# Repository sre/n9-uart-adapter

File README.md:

# N9 UART/Debug Adapter

Kernel developers like to have UART access to their embedded boards for
debugging purposes. While the Nokia N900 and N950 had the pads available
under their battery, Nokia N9 has them inside its SIM-card slot. This
project contains PCB design for KiCAD, which can be used to access the
UART pads.

To get the PCB into a functional state so called "spring fingers" must
be soldered to the rectangular pads.

# License

ISC License

Copyright (c) 2017 Sebastian Reichel <sre@kernel.org>

Permission to use, copy, modify, and/or distribute this software for any
purpose with or without fee is hereby granted, provided that the above
copyright notice and this permission notice appear in all copies.

THE SOFTWARE IS PROVIDED "AS IS" AND THE AUTHOR DISCLAIMS ALL WARRANTIES WITH
REGARD TO THIS SOFTWARE INCLUDING ALL IMPLIED WARRANTIES OF MERCHANTABILITY
AND FITNESS. IN NO EVENT SHALL THE AUTHOR BE LIABLE FOR ANY SPECIAL, DIRECT,
INDIRECT, OR CONSEQUENTIAL DAMAGES OR ANY DAMAGES WHATSOEVER RESULTING FROM
LOSS OF USE, DATA OR PROFITS, WHETHER IN AN ACTION OF CONTRACT, NEGLIGENCE
OR OTHER TORTIOUS ACTION, ARISING OUT OF OR IN CONNECTION WITH THE USE OR
PERFORMANCE OF THIS SOFTWARE.

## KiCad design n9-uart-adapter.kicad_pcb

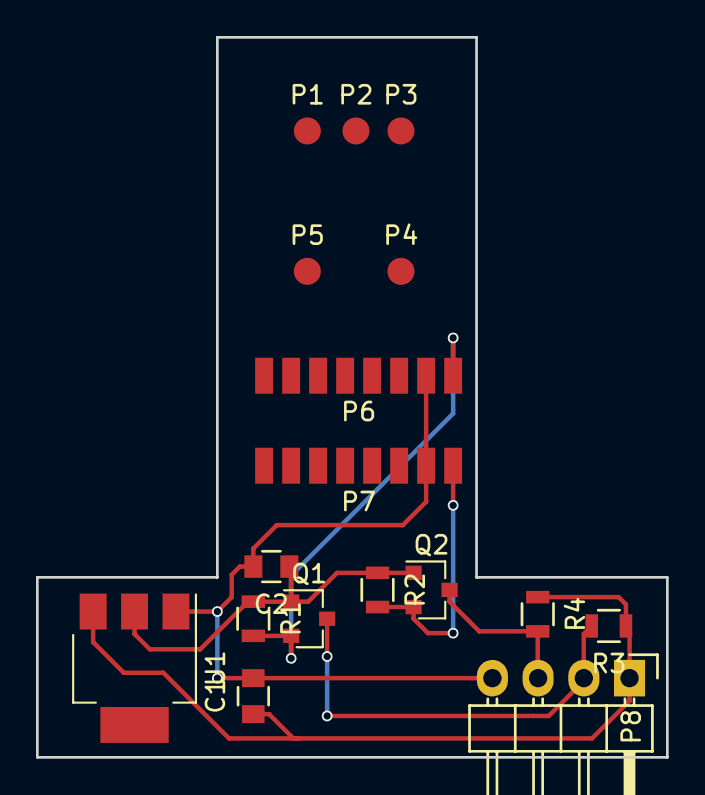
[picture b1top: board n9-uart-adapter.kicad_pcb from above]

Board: 2 copper layers, 35.0 x 40.0 mm, 17 parts (0 on the bottom side), 7 nets.

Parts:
C1: 100nF; C_0805
C2: 10uF; C_0805
P1, P2, P3, P4, P5: PAD; Measurement_Point_Round-SMD-Pad_Small
P6: SPRING_FINGERS_1; Pad-Array
P7: SPRING_FINGERS_2; Pad-Array
P8: CONN_01X04; Pin_Header_Angled_1x04
Q1, Q2: BSS138; SOT-23
R1, R2, R3, R4: 10k; R_0805
U1: LD1117S18CTR; SOT-223

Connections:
+1V8: C2.1, Q1.1, Q2.1, R1.1, R2.1, U1.2
+5V: C1.1, P8.1, R3.1, R4.1, U1.3
/PC_UART_RX: P8.3, Q2.3, R4.2
/PC_UART_TX: P8.2, Q1.3, R3.2
/UART3_RX: P6.8, Q1.2, R1.2
/UART3_TX: P7.8, Q2.2, R2.2
GND: C1.2, C2.2, P6.7, P7.7, P8.4, U1.1

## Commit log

2017-04-19 initial project
2017-04-19 add README
2017-04-19 add SVG, that contains vectorized information from the scan
